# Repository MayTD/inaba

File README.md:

# Inaba 
An open source 40% keyboard with a rotary encoder. Loosely designed by retro TVs and inspired by Persona 4's Midnight Channel.

> [The Midnight Channel (マヨナカテレビ, Mayonaka Terebi), also known as the TV World and Mayonaka TV, is a recurring term in Persona 4. The stuff of urban legends, its existence is spread through the town of Inaba through rumors.](https://megamitensei.fandom.com/wiki/Midnight_Channel)

## Assembly
Components needed for the pcb to be functional or completed.
| Part Number | Qty | Description | Component Reference |
| - | - | - | - |
| ATMEGA32U4-AU | 1 | IC MCU 8BIT 32KB FLASH 44TQFP | U1 |
| PRTR5V0U2X,215 | 1 | TVS DIODE 5.5VWM SOT143B | U2 |
| USB4105-GF-A | 1 | USB-C (USB TYPE-C) USB 2.0 Receptacle | J1 |
| 1N4148W-HE3-08 | 50 | DIODE GEN PURP 75V 150MA SOD123 | D1-D50 |
| WS2812B 5050 RGB LED | 1 | 5mm x 5mm RGB LED | LED1 |
| CX3225SB16000D0GZJC1 | 1 | CRYSTAL 16.0000MHZ 8PF SMD | Y1 |
| ERA-6AEB103V | 2 | RES 10K OHM 0.1% 1/8W 0805 | R1, R4 |
| ERJ-6GEYJ220V | 2 | RES SMD 22 OHM 5% 1/8W 0805 | R2-R3 |
| RC2012J512CS |2| RES SMD 5.1K OHM 5% 1/8W 0805 | R5-R6 |
| CRGCQ0805F330R | 1 | RES 330 OHM 1% 1/8W 0805 | R7 |
| CL21B105KAFNNNE | 1 | CAP CER 1UF 25V X7R 0805 | C1 |
| CL21B104MBCNNNC | 3 | CAP CER 0.1UF 50V X7R 0805 | C2-C4 |
| CL21A106KOQNNNG | 1 | CAP CER 10UF 16V X5R 0805 | C5 |
| CL21C220JB61PNC | 2 | CAP CER 22PF 50V C0G/NP0 0805 | C6-C7 |
| B3U-1000P | 1  | SWITCH TACTILE SPST-NO 0.05A 12V | SW1 |
| 0ZCJ0050AF2E | 1  | PTC RESET FUSE 24V 500MA 1206 | F1 |

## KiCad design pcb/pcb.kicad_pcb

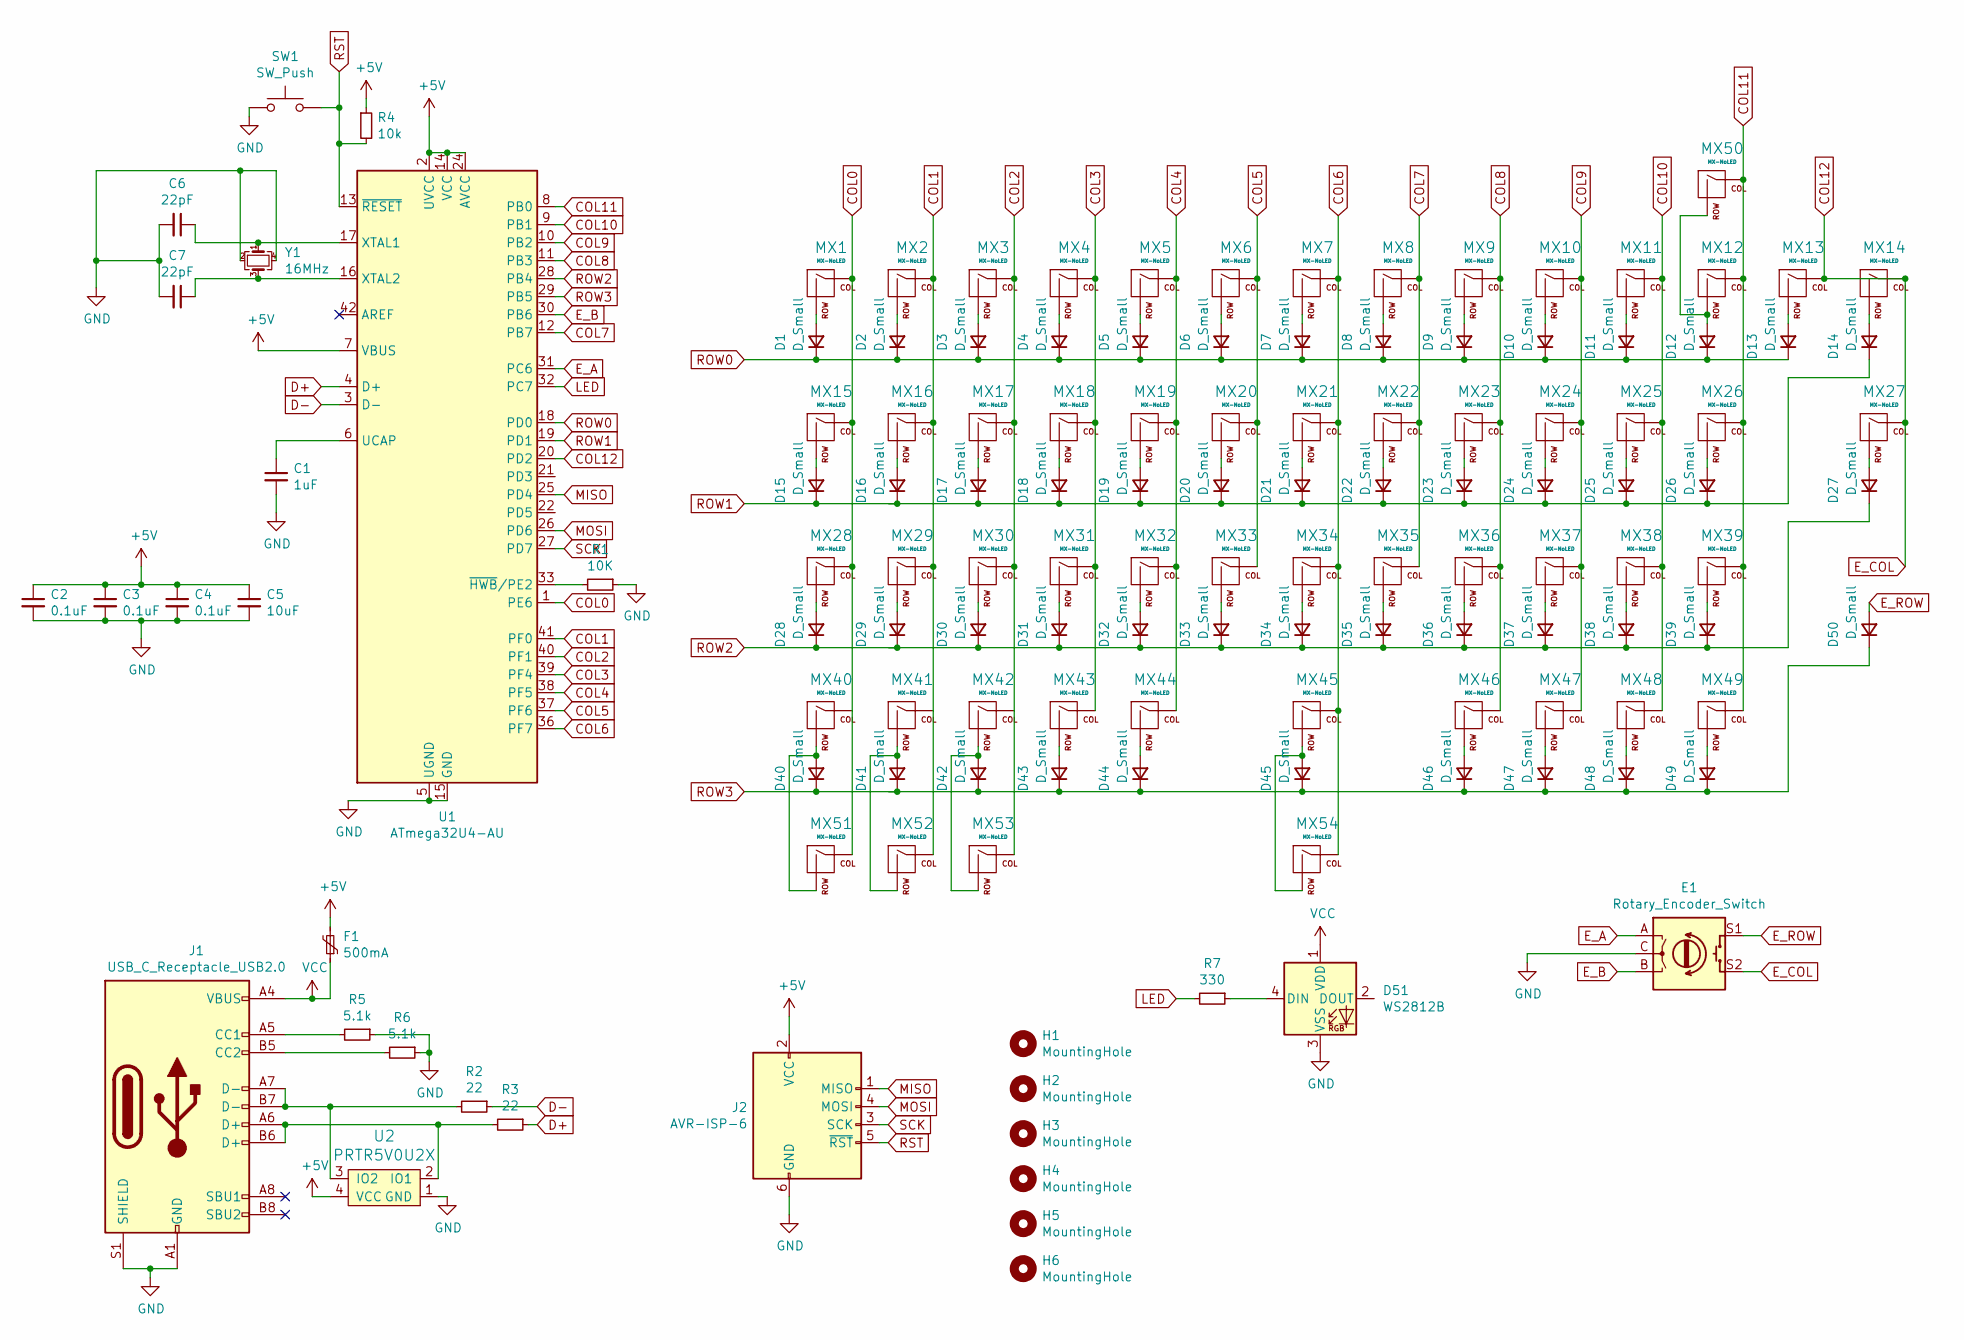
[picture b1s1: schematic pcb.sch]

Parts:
C1: 1uF; C_0805_2012Metric
C2, C3, C4: 0.1uF; C_0805_2012Metric
C5: 10uF; C_0805_2012Metric
C6, C7: 22pF; C_0805_2012Metric
D1, D2, D3, D4, D5, D6, D7, D8, D9, D10, D11, D12, D13, D14, D15, D16, D17, D18, D19, D20, D21, D22, D23, D24, D25, D26, D27, D28, D29, D30, D31, D32, D33, D34, D35, D36, D37, D38, D39, D40, D41, D42, D43, D44, D45, D46, D47, D48, D49, D50: D_Small; D_SOD-123
D51: WS2812B; LED_WS2812B_PLCC4_5.0x5.0mm_P3.2mm
E1: Rotary_Encoder_Switch; RotaryEncoder_Alps_EC11E-Switch_Vertical_H20mm_CircularMoun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
F1: 500mA; Fuse_1206_3216Metric
H1, H2, H3, H4, H5, H6: MountingHole; MountingHole_2.2mm_M2_Pad
J1: USB_C_Receptacle_USB2.0; USB_C_Receptacle_Palconn_UTC16-G
J2: AVR-ISP-6; Reset_Pretty-Mask
MX1, MX2, MX3, MX4, MX5, MX6, MX7, MX8, MX9, MX10, MX11, MX12, MX13, MX14, MX16, MX17, MX18, MX19, MX20, MX21, MX22, MX23, MX24, MX25, MX27, MX29, MX30, MX31, MX32, MX33, MX34, MX35, MX36, MX37, MX38, MX40, MX41, MX42, MX43, MX46, MX47, MX48, MX49: MX-NoLED; MX-1U-NoLED
MX15, MX26: MX-NoLED; MX-1.5U-NoLED
MX28: MX-NoLED; MX-1.75U-NoLED
MX39, MX51, MX52, MX53: MX-NoLED; MX-1.25U-NoLED
MX44: MX-NoLED; MX-2.25U-ReversedStabilizers-NoLED
MX45: MX-NoLED; MX-2.75U-ReversedStabilizers-NoLED
MX50: MX-NoLED; MX-2U-NoLED
MX54: MX-NoLED; MX-6U-Centered-ReversedStabilizers-NoLED
R1: 10K; R_0805_2012Metric
R2, R3: 22; R_0805_2012Metric
R4: 10k; R_0805_2012Metric
R5, R6: 5.1k; R_0805_2012Metric
R7: 330; R_0805_2012Metric
SW1: SW_Push; SW_SPST_B3U-1000P-B
U1: ATmega32U4-AU; TQFP-44_10x10mm_P0.8mm
U2: PRTR5V0U2X; SOT143B
Y1: 16MHz; Crystal_SMD_3225-4Pin_3.2x2.5mm

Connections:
+5V: C2.1, C3.1, C4.1, C5.1, F1.2, J2.2 (VCC), R4.1, U1.2 (UVCC), U1.7 (VBUS), U1.14 (VCC), U1.24 (AVCC), U1.34 (VCC), U1.44 (AVCC), U2.4 (VCC)
COL0: MX1.1 (COL), MX15.1 (COL), MX28.1 (COL), MX40.1 (COL), MX51.1 (COL), U1.1 (PE6)
COL1: MX2.1 (COL), MX16.1 (COL), MX29.1 (COL), MX41.1 (COL), MX52.1 (COL), U1.41 (PF0)
COL2: MX3.1 (COL), MX17.1 (COL), MX30.1 (COL), MX42.1 (COL), MX53.1 (COL), U1.40 (PF1)
COL3: MX4.1 (COL), MX18.1 (COL), MX31.1 (COL), MX43.1 (COL), U1.39 (PF4)
COL4: MX5.1 (COL), MX19.1 (COL), MX32.1 (COL), MX44.1 (COL), U1.38 (PF5)
COL5: MX6.1 (COL), MX20.1 (COL), MX33.1 (COL), U1.37 (PF6)
COL6: MX7.1 (COL), MX21.1 (COL), MX34.1 (COL), MX45.1 (COL), MX54.1 (COL), U1.36 (PF7)
COL7: MX8.1 (COL), MX22.1 (COL), MX35.1 (COL), U1.12 (PB7)
COL8: MX9.1 (COL), MX23.1 (COL), MX36.1 (COL), MX46.1 (COL), U1.11 (PB3)
COL9: MX10.1 (COL), MX24.1 (COL), MX37.1 (COL), MX47.1 (COL), U1.10 (PB2)
COL10: MX11.1 (COL), MX25.1 (COL), MX38.1 (COL), MX48.1 (COL), U1.9 (PB1)
COL11: MX12.1 (COL), MX26.1 (COL), MX39.1 (COL), MX49.1 (COL), MX50.1 (COL), U1.8 (PB0)
COL12: E1.S2, MX13.1 (COL), MX14.1 (COL), MX27.1 (COL), U1.20 (PD2)
D+: R3.1, U1.4 (D+)
D-: R2.1, U1.3 (D-)
E_A: E1.A, U1.31 (PC6)
E_B: E1.B, U1.30 (PB6)
E_ROW: D50.2 (A), E1.S1
GND: C1.2, C2.2, C3.2, C4.2, C5.2, C6.2, C7.2, D51.3 (VSS), E1.C, J1.A1 (GND), J1.A12 (GND), J1.B1 (GND), J1.B12 (GND), J1.S1 (SHIELD), J2.6 (GND), R1.1, R5.1, R6.1, SW1.1, U1.5 (UGND), U1.15 (GND), U1.23 (GND), U1.35 (GND), U1.43 (GND), U2.1 (GND), Y1.2, Y1.4; also elsewhere on the board
LED: R7.2, U1.32 (PC7)
MISO: J2.1 (MISO), U1.25 (PD4)
MOSI: J2.4 (MOSI), U1.26 (PD6)
unnamed: C1.1, U1.6 (UCAP)
unnamed: C6.1, U1.17 (XTAL1), Y1.1
unnamed: C7.1, U1.16 (XTAL2), Y1.3
unnamed: D1.2 (A), MX1.2 (ROW)
unnamed: D2.2 (A), MX2.2 (ROW)
unnamed: D3.2 (A), MX3.2 (ROW)
unnamed: D4.2 (A), MX4.2 (ROW)
unnamed: D5.2 (A), MX5.2 (ROW)
unnamed: D6.2 (A), MX6.2 (ROW)
unnamed: D7.2 (A), MX7.2 (ROW)
unnamed: D8.2 (A), MX8.2 (ROW)
unnamed: D9.2 (A), MX9.2 (ROW)
unnamed: D10.2 (A), MX10.2 (ROW)
unnamed: D11.2 (A), MX11.2 (ROW)
unnamed: D12.2 (A), MX12.2 (ROW), MX50.2 (ROW)
unnamed: D13.2 (A), MX13.2 (ROW)
unnamed: D14.2 (A), MX14.2 (ROW)
unnamed: D15.2 (A), MX15.2 (ROW)
unnamed: D16.2 (A), MX16.2 (ROW)
unnamed: D17.2 (A), MX17.2 (ROW)
unnamed: D18.2 (A), MX18.2 (ROW)
unnamed: D19.2 (A), MX19.2 (ROW)
unnamed: D20.2 (A), MX20.2 (ROW)
unnamed: D21.2 (A), MX21.2 (ROW)
unnamed: D22.2 (A), MX22.2 (ROW)
unnamed: D23.2 (A), MX23.2 (ROW)
unnamed: D24.2 (A), MX24.2 (ROW)
unnamed: D25.2 (A), MX25.2 (ROW)
unnamed: D26.2 (A), MX26.2 (ROW)
unnamed: D27.2 (A), MX27.2 (ROW)
unnamed: D28.2 (A), MX28.2 (ROW)
unnamed: D29.2 (A), MX29.2 (ROW)
unnamed: D30.2 (A), MX30.2 (ROW)
unnamed: D31.2 (A), MX31.2 (ROW)
unnamed: D32.2 (A), MX32.2 (ROW)
unnamed: D33.2 (A), MX33.2 (ROW)
unnamed: D34.2 (A), MX34.2 (ROW)
unnamed: D35.2 (A), MX35.2 (ROW)
unnamed: D36.2 (A), MX36.2 (ROW)
unnamed: D37.2 (A), MX37.2 (ROW)
unnamed: D38.2 (A), MX38.2 (ROW)
unnamed: D39.2 (A), MX39.2 (ROW)
unnamed: D40.2 (A), MX40.2 (ROW), MX51.2 (ROW)
unnamed: D41.2 (A), MX41.2 (ROW), MX52.2 (ROW)
unnamed: D42.2 (A), MX42.2 (ROW), MX53.2 (ROW)
unnamed: D43.2 (A), MX43.2 (ROW)
unnamed: D44.2 (A), MX44.2 (ROW)
unnamed: D45.2 (A), MX45.2 (ROW), MX54.2 (ROW)
unnamed: D46.2 (A), MX46.2 (ROW)
unnamed: D47.2 (A), MX47.2 (ROW)
unnamed: D48.2 (A), MX48.2 (ROW)
unnamed: D49.2 (A), MX49.2 (ROW)
unnamed: J1.A5 (CC1), R5.2
unnamed: J1.A6 (D+), J1.B6 (D+), R3.2, U2.2 (IO1)
unnamed: J1.A7 (D-), J1.B7 (D-), R2.2, U2.3 (IO2)
unnamed: J1.B5 (CC2), R6.2
unnamed 82: D51.4 (DIN), R7.1; also elsewhere on the board
unnamed: R1.2, U1.33 (~HWB~/PE2)
ROW0: D1.1 (K), D2.1 (K), D3.1 (K), D4.1 (K), D5.1 (K), D6.1 (K), D7.1 (K), D8.1 (K), D9.1 (K), D10.1 (K), D11.1 (K), D12.1 (K), D13.1 (K), U1.18 (PD0)
ROW1: D14.1 (K), D15.1 (K), D16.1 (K), D17.1 (K), D18.1 (K), D19.1 (K), D20.1 (K), D21.1 (K), D22.1 (K), D23.1 (K), D24.1 (K), D25.1 (K), D26.1 (K), U1.19 (PD1)
ROW2: D27.1 (K), D28.1 (K), D29.1 (K), D30.1 (K), D31.1 (K), D32.1 (K), D33.1 (K), D34.1 (K), D35.1 (K), D36.1 (K), D37.1 (K), D38.1 (K), D39.1 (K), U1.28 (PB4)
ROW3: D40.1 (K), D41.1 (K), D42.1 (K), D43.1 (K), D44.1 (K), D45.1 (K), D46.1 (K), D47.1 (K), D48.1 (K), D49.1 (K), D50.1 (K), U1.29 (PB5)
RST: J2.5 (~RST), R4.2, SW1.2, U1.13 (~RESET)
SCK: J2.3 (SCK), U1.27 (PD7)
VCC: D51.1 (VDD), F1.1, J1.A4 (VBUS), J1.A9 (VBUS), J1.B4 (VBUS), J1.B9 (VBUS); also elsewhere on the board

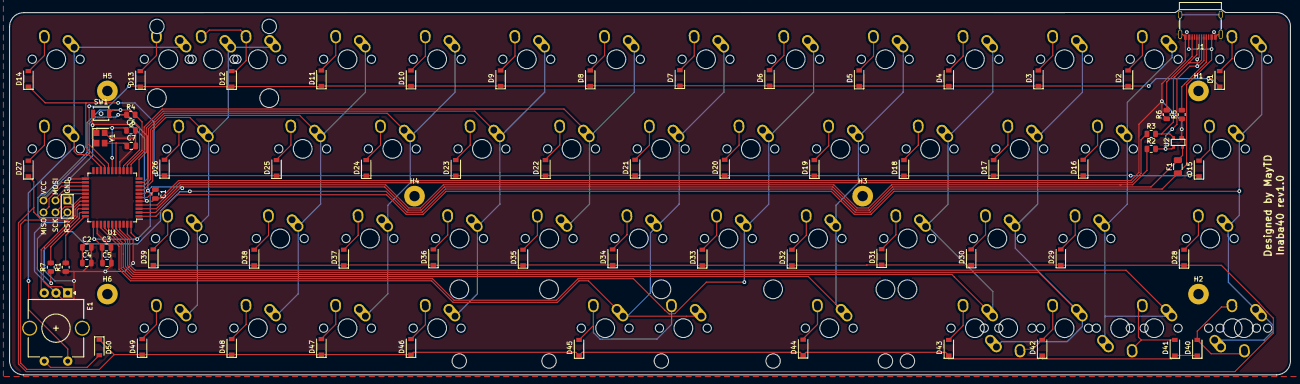
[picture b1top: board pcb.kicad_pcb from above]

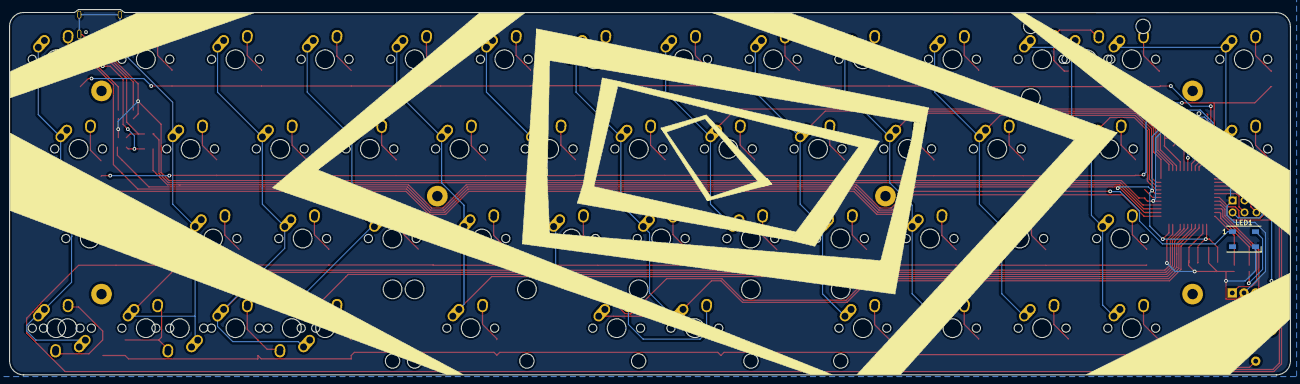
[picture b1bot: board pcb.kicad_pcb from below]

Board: 2 copper layers, 272.3 x 77.6 mm, 133 parts (55 on the bottom side), 88 nets.

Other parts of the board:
LED1: WS2812B; LED_WS2812B_PLCC4_5.0x5.0mm_P3.2mm

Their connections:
GND: LED1.3; also elsewhere on the board
unnamed 82: LED1.4; also elsewhere on the board
VCC: LED1.1; also elsewhere on the board

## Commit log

2021-12-02 keyboard layout JSON
2021-12-03 add footprint libs
2021-12-05 set up mcu and pcb
2021-12-06 set up switch matrix
2021-12-11 assign footprints
2021-12-12 add isp footprints
2021-12-12 iso mask footprint
2021-12-13 change iscp mask footprint
2021-12-31 route tracks
2022-01-04 create bottom plate
2022-01-05 add mounting holes to sch
2022-01-05 correct spacebar placements
2022-01-06 flip stabs on space
2022-01-06 3mm outer spacing
2022-01-07 center isp and reroute tracks
2022-01-08 add LED and reshape width of macros spacer
2022-01-08 gnd zone fill
2022-01-09 create plate
2022-01-09 add silkscreen design to pcb
2022-01-15 move mounting holes and flip silk screen on pcb
2022-01-19 include fuse in assembly component list
2022-01-19 create gerber files
2022-01-20 regenerate gerber
2022-01-21 regenerate gerber removing x2 option
2022-02-25 create gerber zips
